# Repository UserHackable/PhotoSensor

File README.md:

# User Hackable Photo Sensor
A Photo sensor board for use in line following etc.. 

## PhotoSensor 

### Board dimensions

* (149989, 69961) original units
* (1.4999, 0.6996) inches
* (38.0972, 17.7701) mm

[gerbers](%*_gerber.zip)

| Front | Back |
| --- | --- |
|  |  |

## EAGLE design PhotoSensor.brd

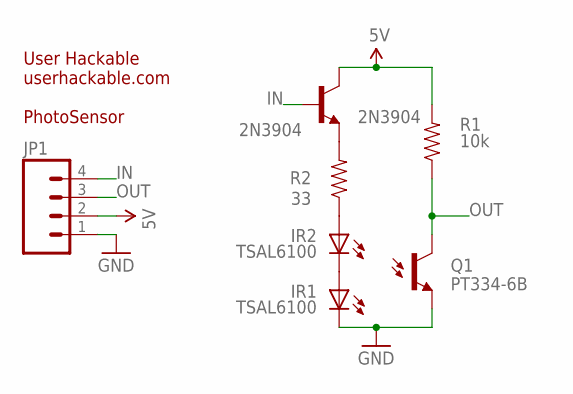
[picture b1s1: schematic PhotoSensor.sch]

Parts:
2N3904: 2N3904; TO-92-AMMO
IR1, IR2: TSAL6100; LED5MM
JP1: M04PTH; 1X04
Q1: PT334-6B; LED5MM
R1: 10k; AXIAL-0.3
R2: 33; AXIAL-0.3

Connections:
5V: 2N3904.3 (C), JP1.2, R1.P$2 (2)
GND: IR1.K (C), JP1.1, Q1.A (E)
IN: 2N3904.2 (B), JP1.4
unnamed: IR1.A, IR2.K (C)
unnamed: IR2.A, R2.P$1 (1)
unnamed: 2N3904.1 (E), R2.P$2 (2)
OUT: JP1.3, Q1.K (C), R1.P$1 (1)

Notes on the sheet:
User Hackable userhackable.com PhotoSensor

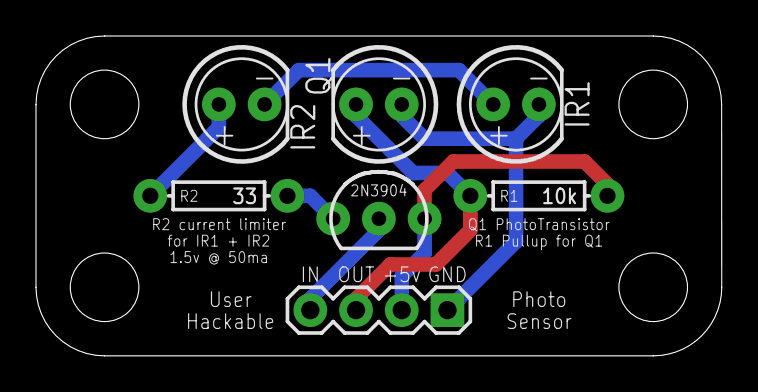
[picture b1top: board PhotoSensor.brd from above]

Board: 2 copper layers, 38.1 x 17.8 mm, 7 parts (0 on the bottom side), 7 nets.

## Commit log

2016-03-23 adding in gerber zip
2016-03-23 removing extra images
2016-03-23 Adding REadme
2016-03-26 updating readme.md
2016-04-06 updating files
2016-04-07 from Makefile
